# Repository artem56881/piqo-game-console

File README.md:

# piqo-game-console
rp2040 game console pcb files and schematic

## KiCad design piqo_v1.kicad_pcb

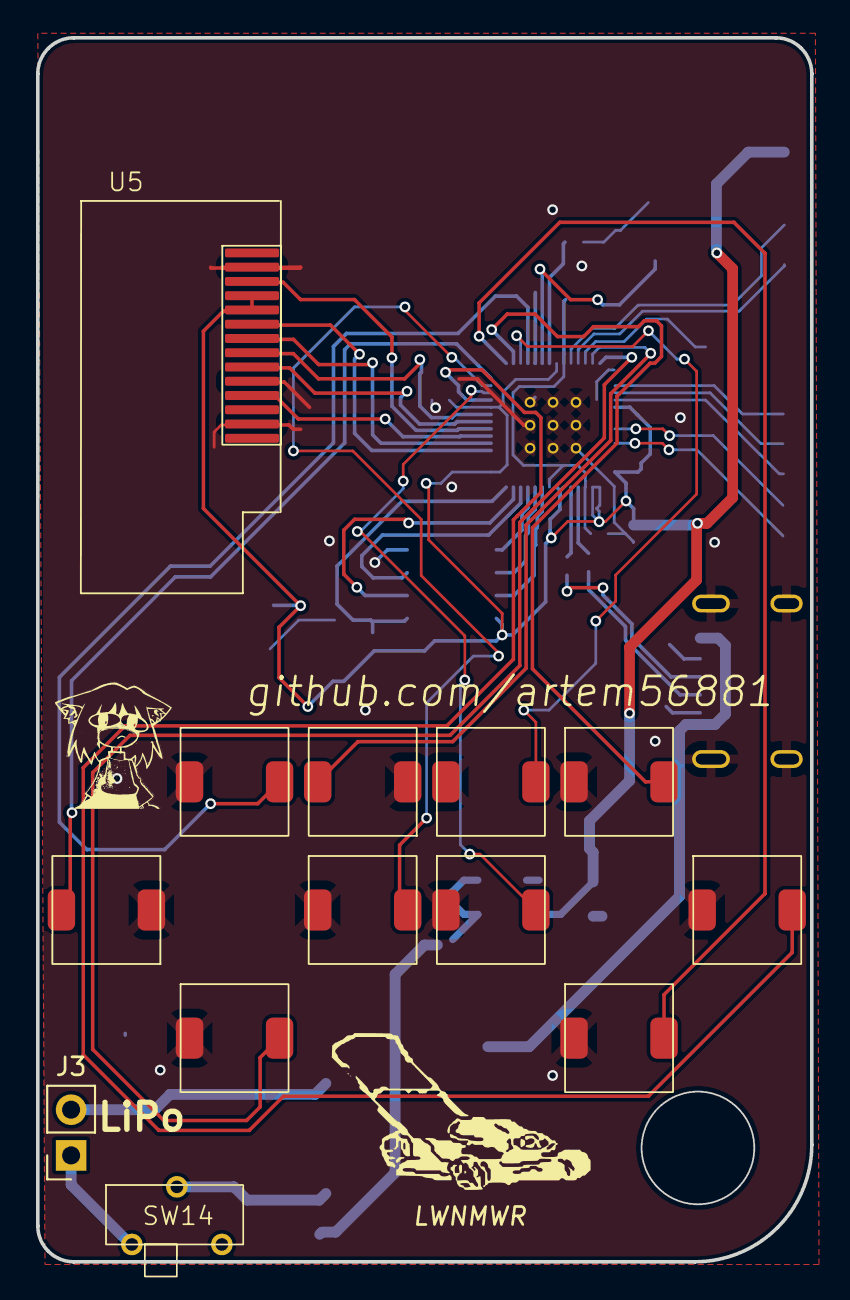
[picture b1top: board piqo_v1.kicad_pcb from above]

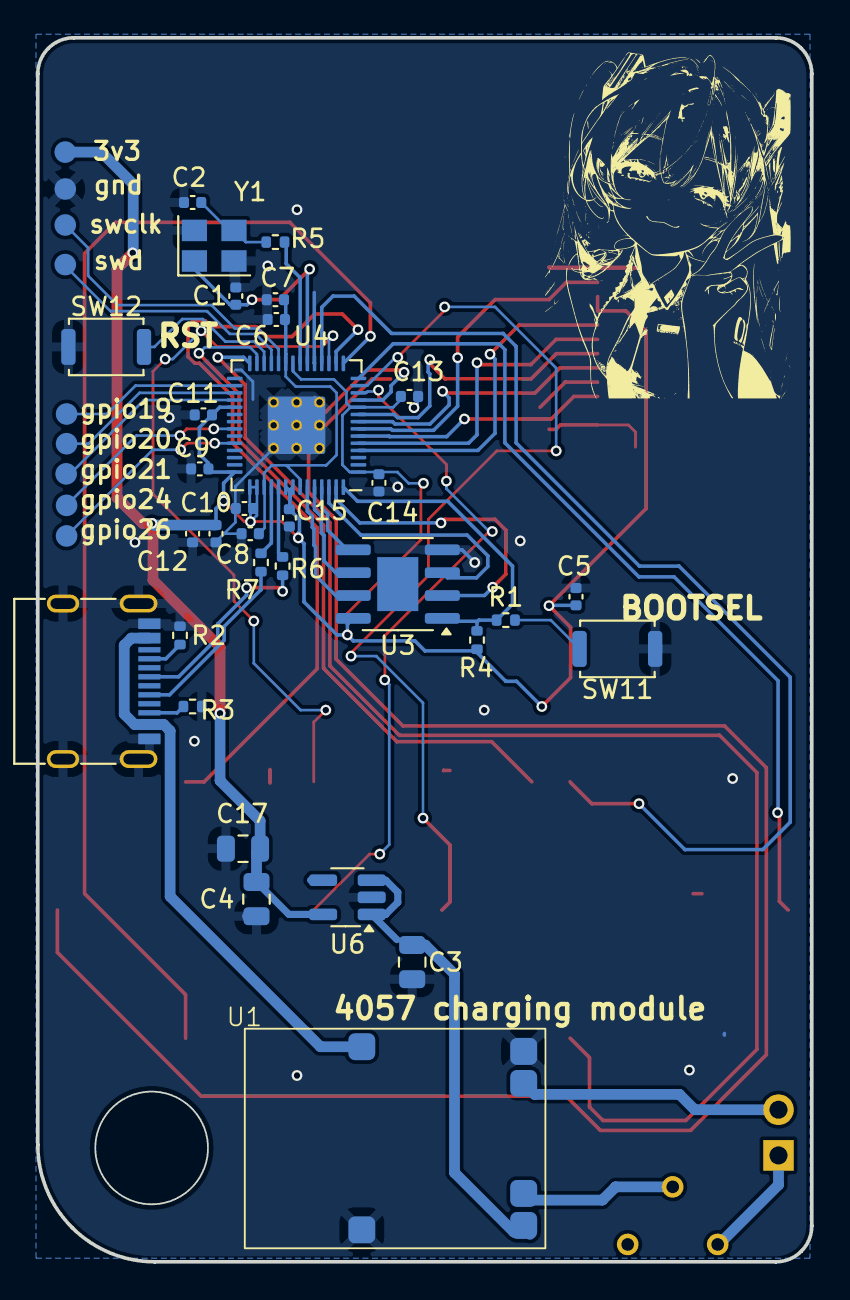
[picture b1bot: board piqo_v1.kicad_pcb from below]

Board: 2 copper layers, 43.0 x 68.0 mm, 49 parts (36 on the bottom side), 44 nets.

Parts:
C1, C2: 15p; C_0402_1005Metric
C3, C4, C17: 10u; C_0805_2012Metric
C5, C6, C7, C9, C11, C12, C13, C14, C15, C16: 100n; C_0402_1005Metric
C8, C10: 1u; C_0402_1005Metric
J2: USB_C_Receptacle_USB2.0_16P; USB_C_Receptacle_G-Switch_GT-USB-7010ASV
J3: Conn_01x02_Pin; PinSocket_1x02_P2.54mm_Vertical
R1, R5: 1k; R_0402_1005Metric
R2, R3: 5.1k; R_0402_1005Metric
R4: DNF; R_0402_1005Metric
R6, R7: 27; R_0402_1005Metric
SW1, SW2, SW3, SW4, SW5, SW6, SW7, SW8, SW9, SW10: SW_Push; rect_silent_button
SW11, SW12: SW_Push; SW_Push_SPST_NO_Alps_SKRK
SW14: SW_Push; mss12d16 3p inline micro switch
U1: 4057charging module
U3: AT25SF081-XMHD-X; SOIC-8-1EP_3.9x4.9mm_P1.27mm_EP2.29x3mm
U4: RP2040; RP2040-QFN-56
U5: st7735_brbns
U6: MCP1802x-xx02xOT; SOT-23-5_HandSoldering
U7, U8, U9, U9#2: pad
Y1: ABM8-272-T3; Crystal_SMD_3225-4Pin_3.2x2.5mm

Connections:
+1V1: C6.1, C7.1, C8.1, U4.23 (DVDD), U4.45 (VREG_VOUT), U4.50 (DVDD)
+3V3: C4.1, C5.1, C9.1, C10.1, C11.1, C12.1, C13.1, C14.1, C15.1, C16.1, C17.1, R4.1, U3.8 (VCC), U4.1 (IOVDD), U4.10 (IOVDD), U4.22 (IOVDD), U4.33 (IOVDD), U4.42 (IOVDD), U4.43 (ADC_AVDD), U4.44 (VREG_IN), U4.48 (USB_VDD), U4.49 (IOVDD), U5.4 (VIN), U5.5 (VIN), U6.5 (VOUT)
/GPIO2: U4.4 (GPIO2), U5.6 (SCK)
/GPIO3: U4.5 (GPIO3), U5.7 (SDA)
/GPIO4: U4.6 (GPIO4), U5.11 (LED)
/GPIO5: U4.7 (GPIO5), U5.3 (CS)
/GPIO6: U4.8 (GPIO6), U5.9 (RST)
/GPIO7: U4.9 (GPIO7), U5.8 (A0)
/GPIO8: SW1.1, U4.11 (GPIO8)
/GPIO9: SW2.1, U4.12 (GPIO9)
/GPIO10: SW3.1, U4.13 (GPIO10)
/GPIO11: SW4.1, U4.14 (GPIO11)
/GPIO12: SW5.1, U4.15 (GPIO12)
/GPIO13: SW6.1, U4.16 (GPIO13)
/GPIO14: SW7.1, U4.17 (GPIO14)
/GPIO15: SW8.1, U4.18 (GPIO15)
/GPIO16: SW9.1, U4.27 (GPIO16)
/GPIO17: SW10.1, U4.28 (GPIO17)
/GPIO19: U4.30 (GPIO19), U9#2.1
/QSPI_SCLK: U3.6 (SCK), U4.52 (QSPI_SCLK)
/QSPI_SD0: U3.5 (SI/IO0), U4.53 (QSPI_SD0)
/QSPI_SD1: U3.2 (SO/IO1), U4.55 (QSPI_SD1)
/QSPI_SD2: U3.3 (~WP/IO2), U4.54 (QSPI_SD2)
/QSPI_SD3: U3.7 (~HOLD/IO3), U4.51 (QSPI_SD3)
/QSPI_SS: R1.1, R4.2, U3.1 (~CS), U4.56 (QSPI_SS)
/RUN: SW12.2, U4.26 (RUN)
/SWCLK: U4.24 (SWCLK), U8.1
/SWD: U4.25 (SWD), U9.1
/USB_D+: J2.A6 (D+), R6.1
/USB_D-: J2.B6 (D+), R7.1
/XIN: C1.1, U4.20 (XIN), Y1.1
/XOUT: R5.1, U4.21 (XOUT)
/~USB_BOOT: R1.2, SW11.2
GND: C1.2, C2.2, C3.2, C4.2, C5.2, C6.2, C7.2, C8.2, C9.2, C10.2, C11.2, C12.2, C13.2, C14.2, C15.2, C16.2, C17.2, J2.A1 (GND), J2.A12 (GND), J2.B1 (GND), J2.B12 (GND), J2.S1 (SHIELD), R2.2, R3.1, SW1.2, SW2.2, SW3.2, SW4.2, SW5.2, SW6.2, SW7.2, SW8.2, SW9.2, SW10.2, SW11.1, SW12.1, U1.1 (out-), U1.6 (in-), U3.4 (GND), U4.19 (TESTEN), U4.57 (GND), U5.2 (GND), U5.10 (GND), U5.13 (GND), U6.2 (GND), U7.1, Y1.2, Y1.4
unnamed: C2.1, R5.2, Y1.3
unnamed: J2.A5 (CC1), R2.1
unnamed: J2.B5 (CC2), R3.2
unnamed: J3.1, SW14.1
unnamed: J3.2, U1.2 (bat-)
unnamed: SW14.2, U1.3 (bat+)
unnamed: C3.1, U1.4 (out+), U6.1 (VIN), U6.3 (~SHDN)
unnamed: R7.2, U4.46 (USB_DM)
unnamed: R6.2, U4.47 (USB_DP)
VBUS: J2.A4 (VBUS), J2.A9 (VBUS), J2.B4 (VBUS), J2.B9 (VBUS), U1.5 (in+)

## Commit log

2025-11-30 changes lol
